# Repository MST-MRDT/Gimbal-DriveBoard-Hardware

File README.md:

# Gimbal-DriveBoard-Hardware
3 Axis Gimbal Controller

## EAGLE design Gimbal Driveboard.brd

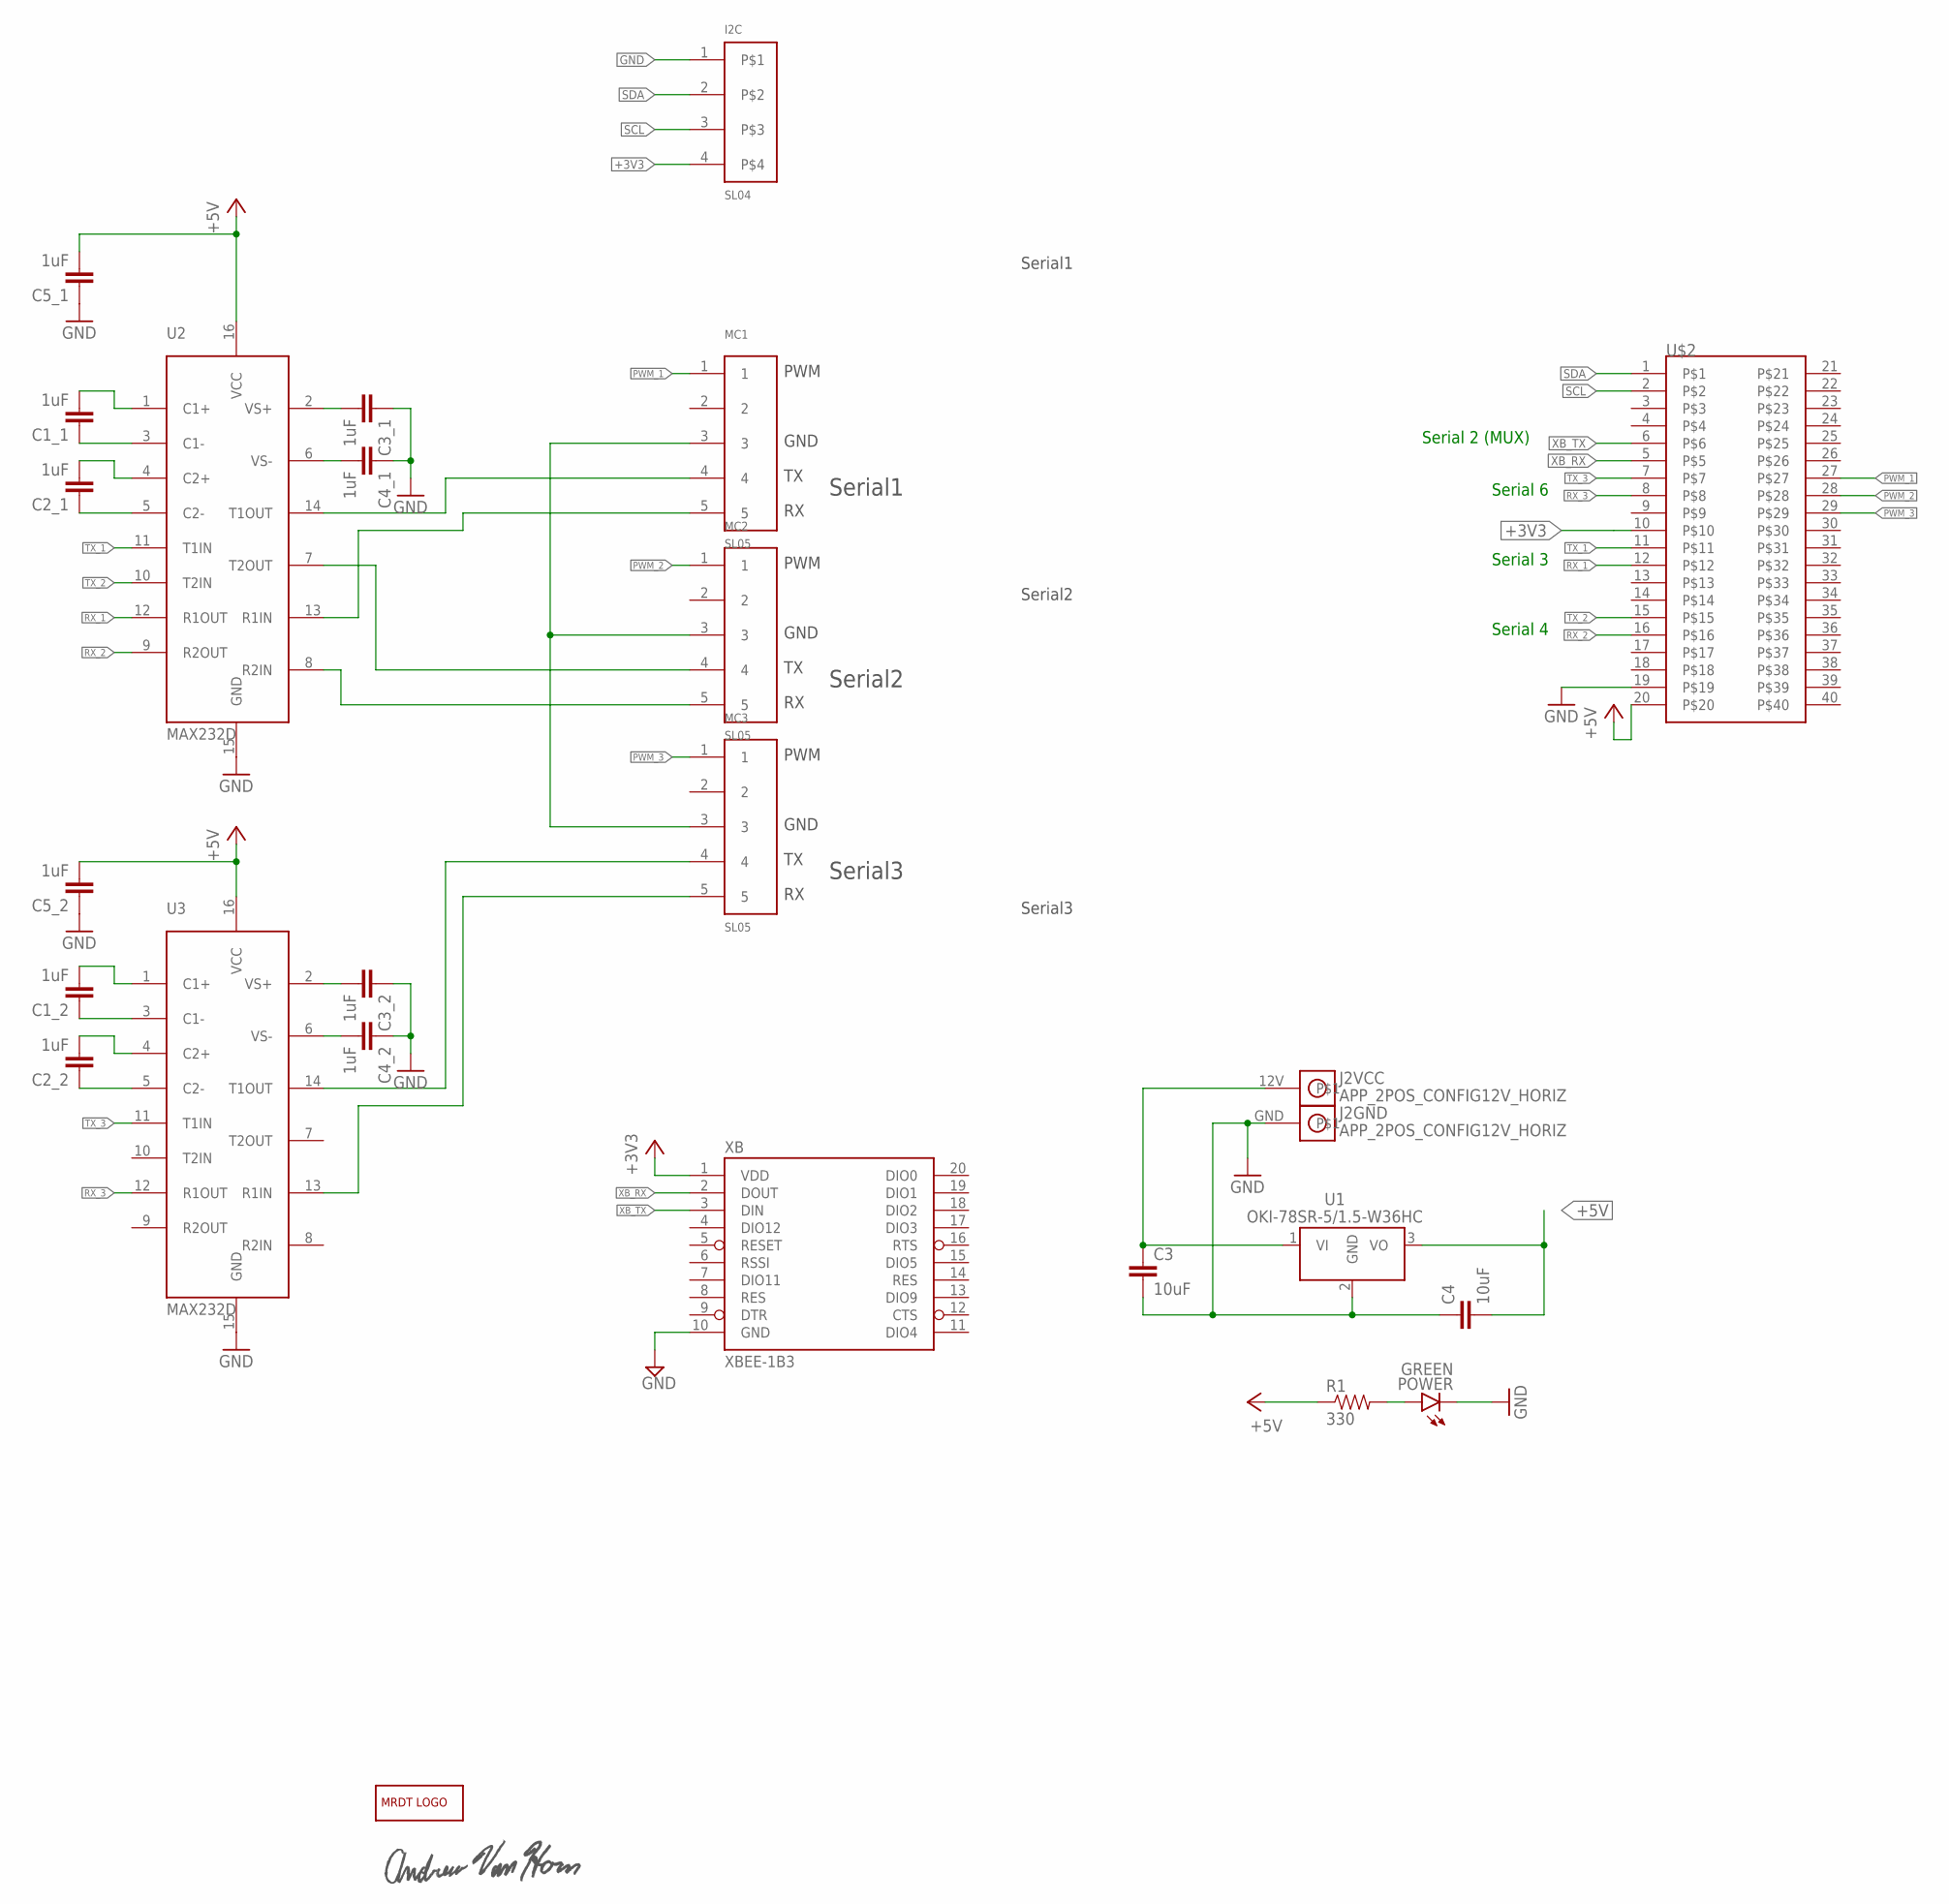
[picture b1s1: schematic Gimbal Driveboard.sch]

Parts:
C1_1, C1_2, C2_1, C2_2, C3_1, C3_2, C4_1, C4_2, C5_1, C5_2: 1uF; 0805
C3, C4: 10uF; 0805
I2C: SL04; MOLEX_SL_04_TH
J2: APP_2POS_CONFIG12V_HORIZ; APP45_12V_HORIZ_CONFIG
LOGO1: MRDT_LOGO
MC1, MC2, MC3: SL05; MOLEX_SL_05_TH
POWER: GREEN; LED-1206
R1: 330; 0805
U1: OKI-78SR-5/1.5-W36HC; OKI-78SR_HORIZ
U2, U3: MAX232D; SOIC16
U$2: TI_BACKPACK_HEADER
U$3: ANDREW_VAN_HORN_SIGNATURE
XB: XBEE-1B3; XBEE-SMD

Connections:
+3V3: I2C.4, U$2.10, XB.1 (VDD)
+5V: C4.2, C5_1.2, C5_2.2, R1.1, U1.3 (VO), U2.16 (VCC), U3.16 (VCC), U$2.20
GND: C3.2, C3_1.1, C3_2.1, C4.1, C4_1.1, C4_2.1, C5_1.1, C5_2.1, I2C.1, J2.GND, MC1.3, MC2.3, MC3.3, POWER.C, U1.2 (GND), U2.15 (GND), U3.15 (GND), U$2.19, XB.10 (GND)
unnamed: C1_1.2, U2.1 (C1+)
unnamed: C1_1.1, U2.3 (C1-)
unnamed: C3.1, J2.12V, U1.1 (VI)
unnamed: C2_1.2, U2.4 (C2+)
unnamed: C2_1.1, U2.5 (C2-)
unnamed: C3_1.2, U2.2 (VS+)
unnamed: C4_1.2, U2.6 (VS-)
unnamed: C1_2.2, U3.1 (C1+)
unnamed: C1_2.1, U3.3 (C1-)
unnamed: C2_2.2, U3.4 (C2+)
unnamed: C3_2.2, U3.2 (VS+)
unnamed: C4_2.2, U3.6 (VS-)
unnamed: C2_2.1, U3.5 (C2-)
unnamed: POWER.A, R1.2
unnamed: MC3.4, U3.14 (T1OUT)
unnamed: MC3.5, U3.13 (R1IN)
unnamed: MC2.5, U2.8 (R2IN)
unnamed: MC2.4, U2.7 (T2OUT)
unnamed: MC1.4, U2.14 (T1OUT)
unnamed: MC1.5, U2.13 (R1IN)
PWM_1: MC1.1, U$2.27
PWM_2: MC2.1, U$2.28
PWM_3: MC3.1, U$2.29
RX_1: U2.12 (R1OUT), U$2.12
RX_2: U2.9 (R2OUT), U$2.16
RX_3: U3.12 (R1OUT), U$2.8
SCL: I2C.3, U$2.2
SDA: I2C.2, U$2.1
TX_1: U2.11 (T1IN), U$2.11
TX_2: U2.10 (T2IN), U$2.15
TX_3: U3.11 (T1IN), U$2.7
XB_RX: U$2.5, XB.2 (DOUT)
XB_TX: U$2.6, XB.3 (DIN)

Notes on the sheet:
Serial1
Serial2
Serial3
PWM
GND
Serial 6
Serial 3
Serial 4
Serial 2 (MUX)

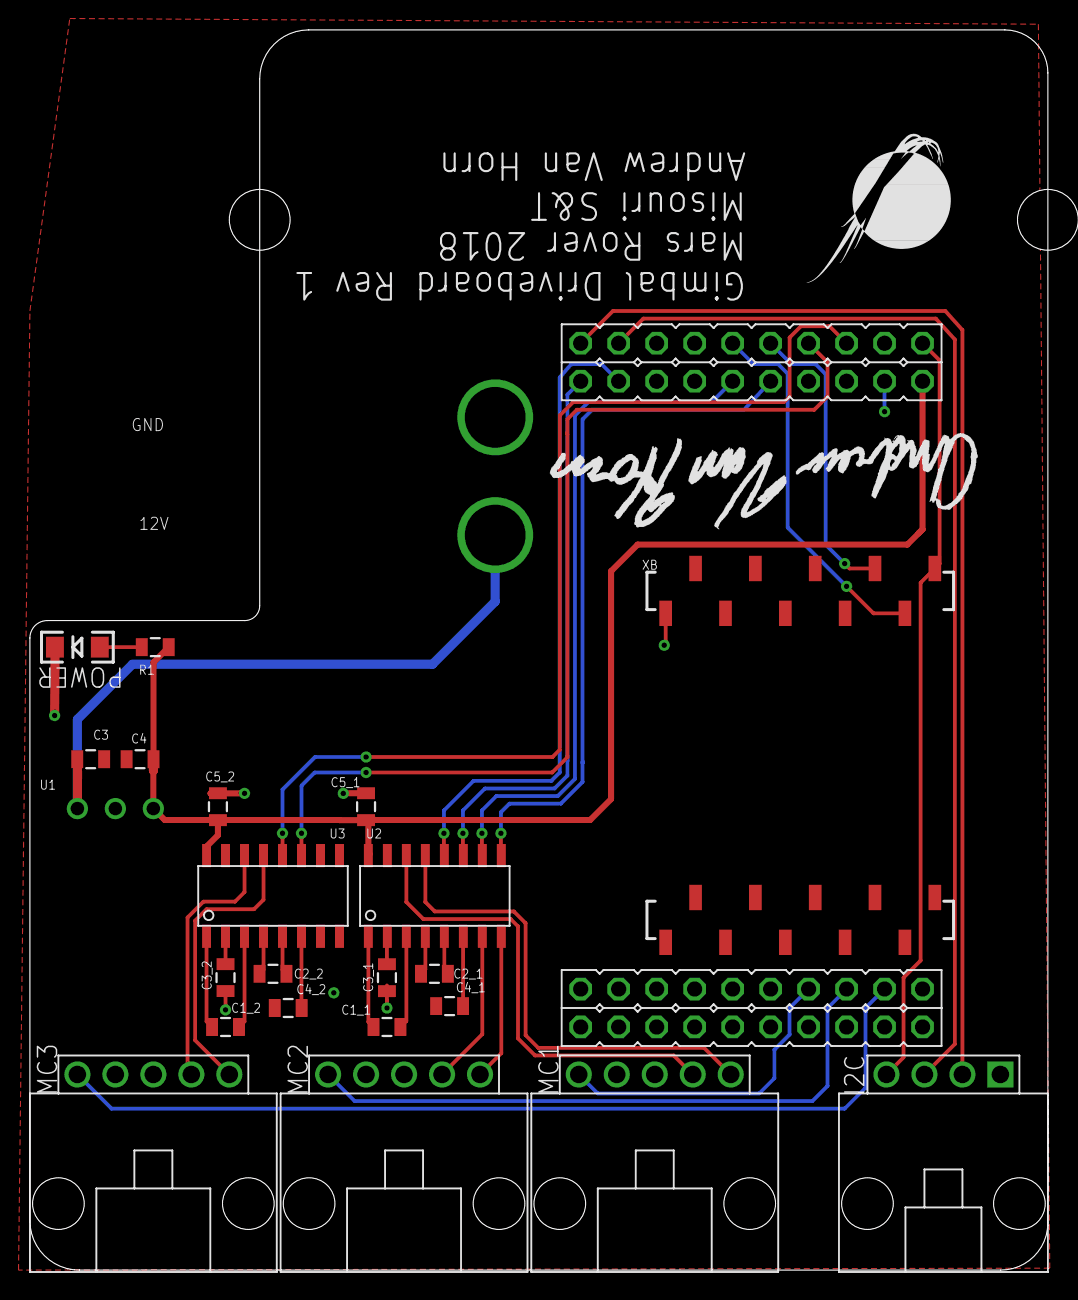
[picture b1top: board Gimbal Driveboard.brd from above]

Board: 2 copper layers, 68.1 x 82.9 mm, 26 parts (0 on the bottom side), 36 nets.

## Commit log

2018-01-11 Created Board
2018-01-14 Created schematic and board Rev 1
    Will update board to avoid physical interference with the Tiva ethernet connector
2018-01-16 Remade schematic to avoid physical interference with ethernet port
2018-01-24 Updated schematic and board for final board review
    added I2C Molex SL4
    Added mounting tab and holes
    cleaned up lines and traces
    Added signature and board information
2018-01-25 Final board review and Rev 1 Gerbs
2018-01-28 removed TIVA holes on outside of board and rotated silkscreen
    I replaced the TIVA package with just the ehaders and re-assigned all the pins in the schematic to match the physical layout on the old package. I rotated the silkscreen 180 so it is oriented right w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
2018-01-28 Increased Notch Size
2018-01-31 Created Gerbs
2018-03-04 Re-routed XB Serial to Serial 2

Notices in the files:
parts and their libraries:
SparkFun-Capacitors: Licensing: Creative Commons ShareAlike 4.0 International - https://creativecommons.org/licenses/by-sa/4.0
